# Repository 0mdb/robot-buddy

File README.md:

# Robot Buddy

A kid-safe, expressive robot platform combining real-time motor control, an animated TFT face, and optional networked AI planner.

## How It Works

Two ESP32-S3 microcontrollers handle the deterministic, safety-critical work: one drives motors with PID control and enforces safety limits, the other renders an animated face on a 320x240 TFT touch display (`esp32-face`). A Raspberry Pi 5 orchestrates everything at 50 Hz — reading sensors, running the state machine, applying layered safety policies, and streaming telemetry to a browser UI. An optional AI planner server on a separate machine (3090 Ti) generates expressive behavior plans via a local LLM.

Reflexes are local and deterministic. Planner is remote and optional.

## Hardware

| Component | Hardware | Role |
|---|---|---|
| Supervisor | Raspberry Pi 5 | 50 Hz orchestration, safety policy, HTTP/WS API |
| Face MCU | ESP32-S3 (Freenove FNK0104) | 320x240 TFT face renderer + touch/buttons telemetry |
| Reflex MCU | ESP32-S3 WROOM | Differential drive, PID, encoders, IMU, ultrasonic, safety |
| AI Server | PC with 3090 Ti (off-robot) | Planner/conversation LLM + TTS on LAN (`LLM_BACKEND=ollama|vllm`) |
| Motor Driver | TB6612FNG | Dual H-bridge for differential drive |
| Power | 2S LiPo | Split into dirty (motors) and clean 5V regulated rails |

## Repository Layout

```
robot-buddy/
├── supervisor/       # Python supervisor (Raspberry Pi 5, process-isolated workers)
│   ├── core/            # 50 Hz tick loop, state machine, safety, behavior engine
│   ├── devices/         # MCU clients (reflex, face), protocol, expressions
│   ├── io/              # Serial transport, COBS framing, CRC
│   ├── workers/         # Process-isolated workers (TTS, vision, AI)
│   ├── messages/        # NDJSON envelope, event/action types
│   ├── api/             # FastAPI HTTP/WebSocket server, param registry
│   ├── mock/            # Mock Reflex MCU for testing (PTY-based)
│   ├── tests/           # pytest test suite
│   └── pyproject.toml   # Package metadata, deps
├── server/              # AI planner server (3090 Ti, FastAPI + backend switch)
│   ├── app/             # FastAPI app, LLM/STT/TTS backends, prompts, schemas
│   ├── tests/           # pytest test suite
│   ├── Modelfile        # Legacy Ollama model config
│   └── pyproject.toml   # Package metadata, deps
├── esp32-face/       # Face MCU firmware (ESP32-S3, C/C++, ESP-IDF)
│   └── main/            # TFT face rendering + touch/buttons + USB protocol
├── esp32-reflex/        # Reflex MCU firmware (ESP32-S3, C/C++, ESP-IDF)
│   └── main/            # Differential drive, PID, IMU, safety, encoders
├── dashboard/           # React dashboard (Vite + TypeScript + Biome)
│   └── src/             # Components, hooks, stores, tabs
├── specs/               # Completed specifications (immutable reference)
├── docs/                # TODO, architecture, protocols, wiring, power, research
├── deploy/              # Deployment (systemd service, install/update scripts)
├── tools/               # Dev utilities (face sim V3, parity check)
└── training/            # Wake word model training
```

## Architecture

```
┌──────────────────────────────────────────────────────┐
│ On Robot                                             │
│                                                      │
│  ┌────────────────────────────────────────────────┐  │
│  │ Raspberry Pi 5 — Supervisor                    │  │
│  │                                                │  │
│  │  50 Hz tick loop:                              │  │
│  │    read telemetry → state machine → safety     │  │
│  │    policies → send commands → broadcast        │  │
│  │                                                │  │
│  │  HTTP API (:8080)  WebSocket (:8080/ws)        │  │
│  │  Vision process (separate OS process, 10-20Hz) │  │
│  └──────┬──────────────────────┬──────────────────┘  │
│         │ USB serial (COBS)    │ USB serial (COBS)   │
│  ┌──────▼──────┐        ┌─────▼───────┐             │
│  │ Reflex MCU  │        │  Face MCU   │             │
│  │ ESP32-S3    │        │  ESP32-S3   │             │
│  │             │        │             │             │
│  │ Motors, PID │        │ 320x240 TFT │             │
│  │ Encoders    │        │ Face +      │             │
│  │ IMU, Range  │        │ Touch UI    │             │
│  │ Safety      │        │             │             │
│  └─────────────┘        └─────────────┘             │
└──────────────────────────────────────────────────────┘
         │
         │ HTTP (LAN, optional)
         │
┌────────▼───────────────────────────┐
│ AI Server (3090 Ti PC)             │
│                                    │
│ FastAPI planner server             │
│ LLM backend: ollama | vllm         │
│ TTS: Orpheus (vLLM) + espeak shed  │
│ POST /plan / WS /converse /tts     │
└────────────────────────────────────┘
```

### State Machine

`BOOT` → `IDLE` → `TELEOP` / `WANDER` → `ERROR`

- **BOOT → IDLE**: automatic when Reflex MCU connects with no faults
- **IDLE → TELEOP/WANDER**: via `set_mode` command
- **Any → ERROR**: on disconnect, ESTOP, TILT, or BROWNOUT
- **ERROR → IDLE**: via `clear_error()` when Reflex is healthy

### Safety Policies (Defense in Depth)

1. Mode gate — no motion outside TELEOP/WANDER
2. Fault gate — any fault → zero twist
3. Reflex disconnect → zero twist
4. Ultrasonic range scaling (hard stop at 250 mm, 50% at 500 mm)
5. Stale range fallback (50% cap)
6. Vision confidence scaling
7. Stale vision timeout (500 ms)

Safety-critical enforcement also runs on the Reflex MCU itself (acceleration limits, command TTL, hard stop). The supervisor applies additional caps above this.

### Serial Protocol

Binary packets over USB serial with COBS framing:

```
[type:u8][seq:u8][payload:N][crc16:u16-LE]
```

For `esp32-face`, this protocol carries face state/gesture/system/talking commands and touch/button/status telemetry only. Audio transport is supervisor-side USB audio.

Auto-reconnect with exponential backoff (0.5s–5s). See `docs/protocols.md` for packet definitions.

## Tech Stack

| Component | Stack |
|---|---|
| Supervisor | Python 3.11+, asyncio, FastAPI, uvicorn, pyserial, OpenCV |
| AI Server | Python 3.11+, FastAPI, httpx, Pydantic, Ollama (compat) + vLLM (migration target) |
| ESP32 Firmware | C/C++, ESP-IDF (FreeRTOS), CMake |
| Build (Python) | Hatchling via pyproject.toml, uv for dependency management |
| Build (ESP32) | `idf.py build` (CMake), `source ~/esp/esp-idf/export.sh` |
| Dashboard | React 19, Vite, TypeScript, Zustand, TanStack Query |
| Tests | pytest, pytest-asyncio, Vitest |
| Linting | ruff (Python), clang-format + cppcheck (C++), Biome (TypeScript) |

## Getting Started

### Supervisor (Raspberry Pi 5)

```bash
cd supervisor
uv sync --group dev

# Run with mock hardware (no physical robot needed)
just run-mock

# Run with real hardware
just run

# Other options
uv run python -m supervisor --no-vision         # Disable vision worker
uv run python -m supervisor --http-port 8080    # Custom HTTP port
uv run python -m supervisor --planner-api http://10.0.0.20:8100 --robot-id robot-1
```

### AI Planner Server (3090 Ti PC)

```bash
# Install and run the server
cd server
uv sync --extra dev --extra llm --extra stt --extra tts

# Recommended testing profile (vLLM planner + CPU STT + espeak)
LLM_BACKEND=vllm STT_DEVICE=cpu TTS_BACKEND=espeak \
uv run --extra llm --extra stt --extra tts python -m app.main
```

The server starts on port 8100. See `server/README.md` for full API docs and configuration.

### ESP32 Firmware

Requires ESP-IDF toolchain.

```bash
cd esp32-face   # or esp32-reflex
idf.py build
idf.py flash
idf.py monitor
```

### Dashboard

```bash
just run-dashboard         # dev server with hot reload
just build-dashboard       # production build → supervisor/static/
```

## Development

All commands are available via `just` (see `justfile`):

```bash
just test-all              # run all tests (supervisor, server, dashboard)
just lint                  # check Python + C++ + dashboard
just lint-fix              # auto-fix formatting
just preflight             # full pre-commit check (lint + tests + parity)
just sim                   # run face simulator V3
just check-parity          # verify sim↔MCU constant alignment
```

### Mock Mode

The supervisor includes a PTY-based mock Reflex MCU (`supervisor/mock/mock_reflex.py`) that simulates serial communication, telemetry, and fault injection. Use `just run-mock` to run the full supervisor stack without any hardware.

### Dashboard

When the supervisor is running, open `http://<robot_ip>:8080` in a browser for:
- Live telemetry display with diagnostic tree
- Mode control (IDLE, TELEOP, WANDER)
- E-STOP button
- Face control (moods, gestures, talking, conversation state)
- Parameter tuning sliders (PID gains, speed limits, safety thresholds)
- Monitor tab (device health, comms, power, sensors, faults, workers)
- MJPEG video stream (if vision enabled)

### Configuration

**Supervisor** — YAML config file (schema in `supervisor/config.py`):
- Sections: serial, control, safety, network, logging, vision
- Default serial paths: `/dev/robot_reflex`, `/dev/robot_face` (via udev symlinks)

**AI Server** — environment variables:
- `LLM_BACKEND`, `VLLM_MODEL_NAME`, `LLM_MAX_INFLIGHT`, `PERFORMANCE_MODE`
- legacy compatibility: `OLLAMA_URL`, `MODEL_NAME`, `PLAN_TIMEOUT_S`, `TEMPERATURE`, `NUM_CTX`
- See `server/README.md` for the full table

**ESP32** — `sdkconfig.defaults` + `config.h` constants

## Supervisor API

| Endpoint | Method | Description |
|---|---|---|
| `/status` | GET | Current robot state (JSON) |
| `/params` | GET | Full parameter registry |
| `/params` | POST | Transactional parameter updates |
| `/actions` | POST | RPC: `set_mode`, `e_stop`, `clear_e_stop` |
| `/video` | GET | MJPEG stream (if vision enabled) |
| `/debug/devices` | GET | Device connection state |
| `/debug/planner` | GET | Planner state |
| `/debug/mcu_benchmark` | GET | MCU benchmark run status |
| `/ws` | WS | Telemetry stream (20 Hz, JSON) |
| `/ws/logs` | WS | Live log stream |

## AI Server API

| Endpoint | Method | Description |
|---|---|---|
| `/health` | GET | Server + selected LLM backend status |
| `/plan` | POST | Accept world state + `robot_id/seq/monotonic_ts_ms`, return plan + `plan_id` echo metadata |
| `/converse` | WS | Conversation stream (single active session per `robot_id`) |
| `/tts` | POST | Direct TTS with optional metadata (`robot_id`, `seq`, `monotonic_ts_ms`) |

Plan actions: `say(text)`, `emote(name, intensity)`, `gesture(name, params)`, `skill(name)` — planner proposes intent and supervisor executes deterministic skills.

## Supervisor Fallback Policy

| Failure condition | Immediate supervisor action | Motion policy | Face policy | Speech policy |
|---|---|---|---|---|
| `/plan` unreachable / non-200 | Mark planner disconnected; skip remote plan apply | Local deterministic only (`patrol_drift`/`avoid_obstacle`/safe stop) | `confused` gesture with cooldown | Cancel queued planner speech |
| `/converse` TTS fails mid-turn | Stop playback and clear talking flag | No change to motion authority | Show `thinking` briefly then restore previous mood | Attempt fallback backend once; if unavailable, skip speech |

## Project Status

### Working
- [x] Supervisor: 50 Hz control loop, state machine, safety policies, conversation state, mood choreography
- [x] Supervisor: serial transport with COBS framing, CRC, auto-reconnect, protocol v2 (timestamps + seq)
- [x] Supervisor: FastAPI HTTP/WebSocket API with telemetry streaming
- [x] Supervisor: process-isolated workers (TTS, vision, AI, ear)
- [x] Supervisor: mock Reflex MCU for hardware-free development
- [x] AI Server: FastAPI + vLLM planner (Qwen), conversation, TTS (Orpheus + espeak)
- [x] ESP32 Face: TFT face rendering, 13 moods, 13 gestures, conversation border, touch/button telemetry
- [x] ESP32 Reflex: motor control, PID, encoders, IMU, safety enforcement
- [x] Dashboard: React 19, live telemetry, face control, monitor tab, mode control
- [x] Voice pipeline: wake word ("hey buddy") + VAD → STT → LLM → TTS → face animation
- [x] WANDER mode driven by deterministic skills + planner intent
- [x] Deterministic telemetry: timestamps, sequence numbers, clock sync, raw packet logging

### In Progress
- [ ] Reflex MCU hardware commissioning (breadboard bring-up)
- [ ] Personality engine implementation (spec complete, implementation pending)

### Future
- [ ] Conversation memory / interaction history
- [ ] Wake word model improvements (recall 42% → 80%+)
- [ ] Additional modes: LINE_FOLLOW, BALL, CRANE, CHARGING
- [ ] Home Assistant integration
- [ ] Voice ID / speaker identification

See [docs/TODO.md](docs/TODO.md) for the detailed backlog and [specs/](specs/) for design specifications.

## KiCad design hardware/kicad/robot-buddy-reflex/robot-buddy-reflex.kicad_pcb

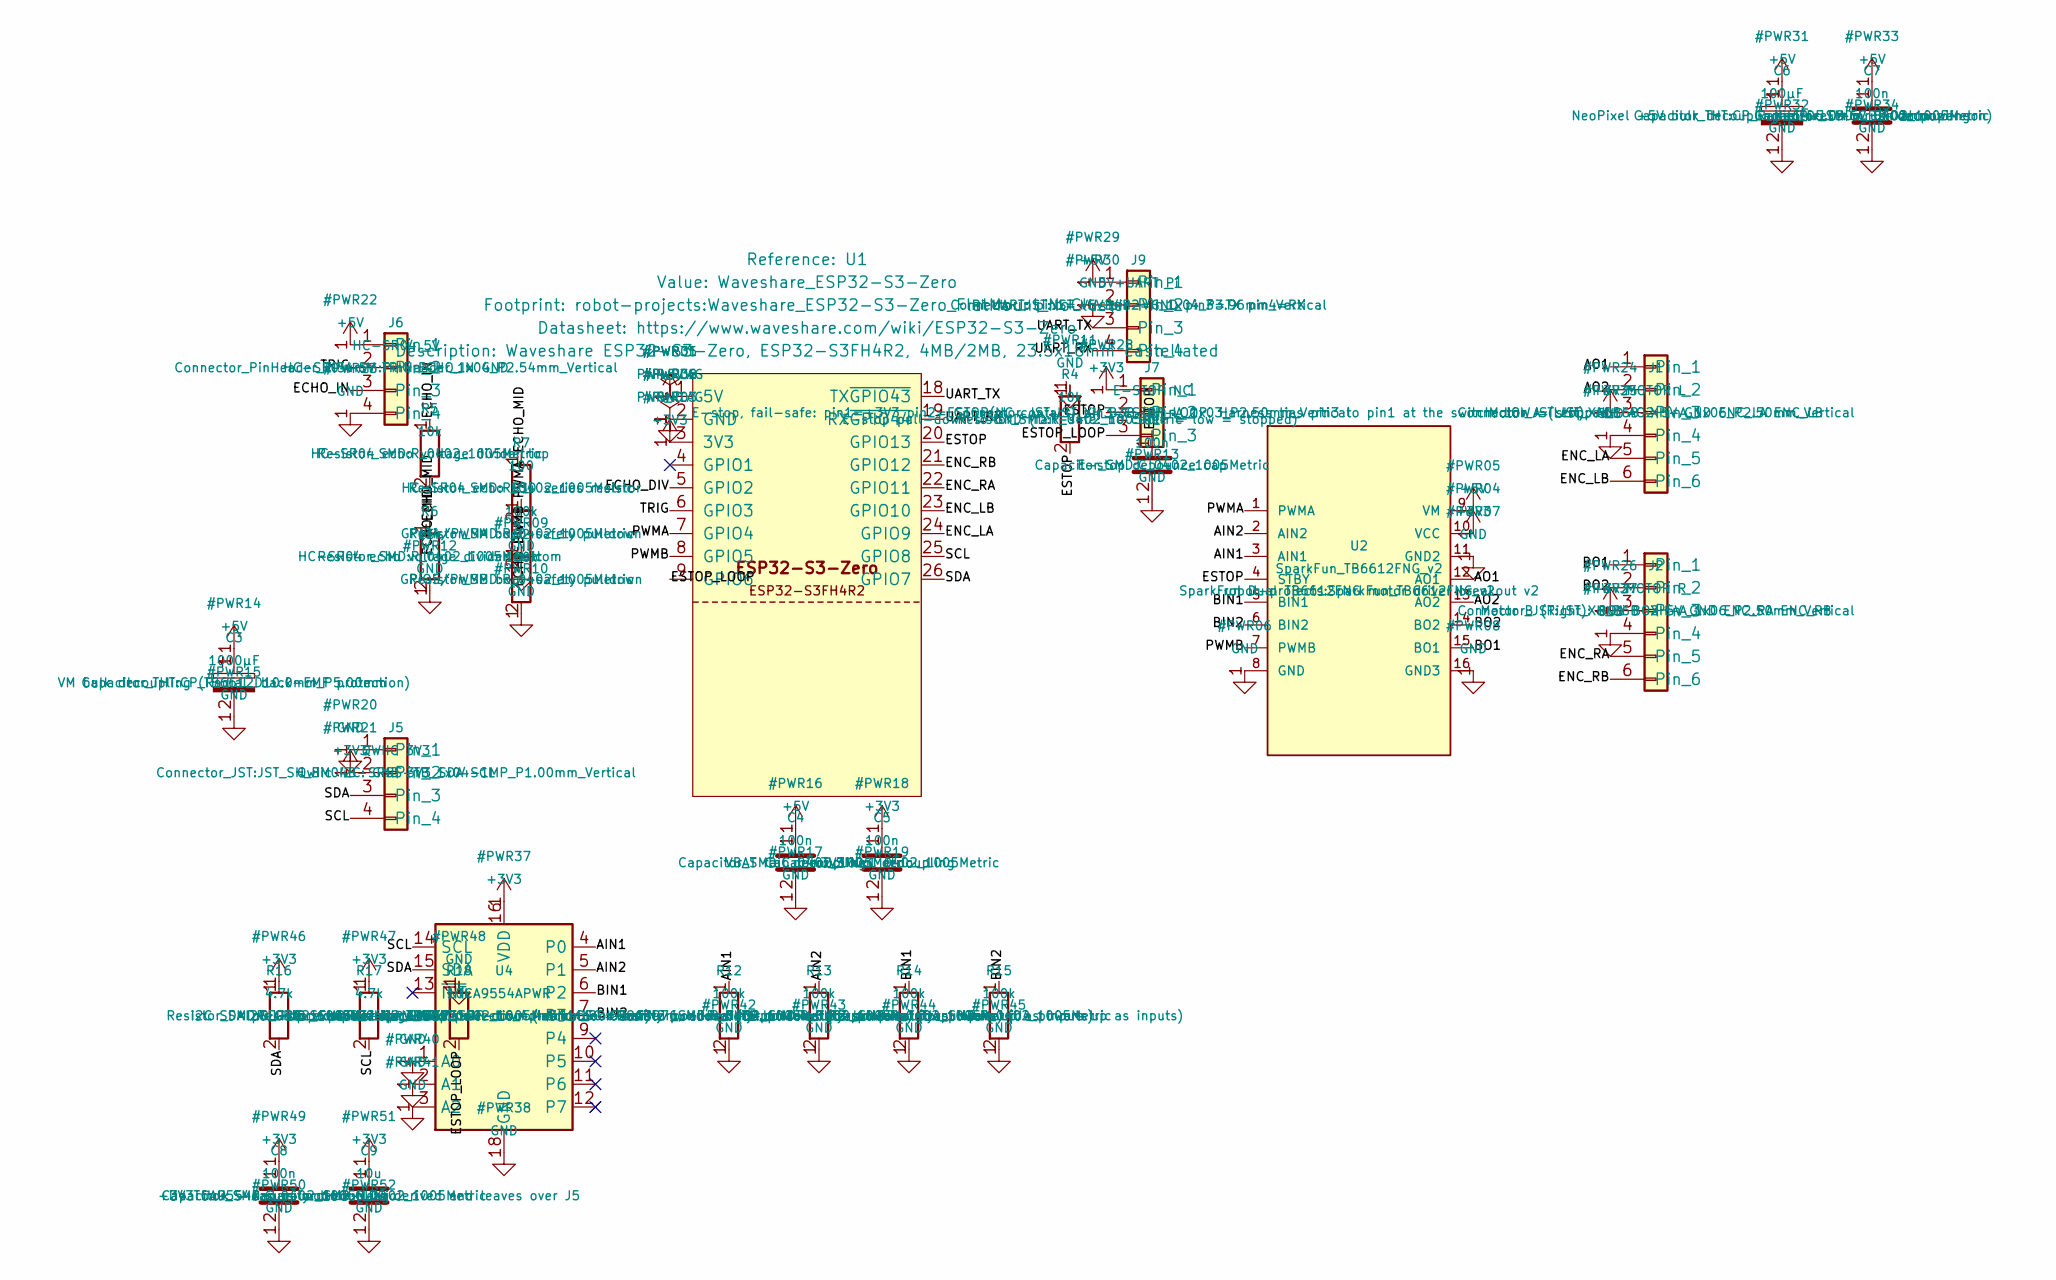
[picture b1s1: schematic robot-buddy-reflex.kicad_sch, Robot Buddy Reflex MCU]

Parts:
C1, C4, C5, C7, C8: 100n; C_0402_1005Metric
C3: 1000µF; CP_Radial_D10.0mm_P5.00mm
C6: 100µF; CP_Radial_D5.0mm_P2.00mm
C9: 10u; C_0402_1005Metric
J1: MOTOR L; JST_XH_B6B-XH-A_1x06_P2.50mm_Vertical
J2: MOTOR R; JST_XH_B6B-XH-A_1x06_P2.50mm_Vertical
J5: QWIIC 3V3; JST_SH_BM04B-SRSS-TB_1x04-1MP_P1.00mm_Vertical
J6: HC-SR04 5V; PinHeader_1x04_P2.54mm_Vertical
J7: E-STOP NC; JST_XH_B3B-XH-A_1x03_P2.50mm_Vertical
J9: 5V+UART Pi; JST_VH_B4P-VH_1x04_P3.96mm_Vertical
R1, R2, R12, R13, R14, R15: 100k; R_0402_1005Metric
R4, R5, R18: 10k; R_0402_1005Metric
R6: 15k; R_0402_1005Metric
R7: 100; R_0402_1005Metric
R16, R17: 4.7k; R_0402_1005Metric
U1: Waveshare_ESP32-S3-Zero; Waveshare_ESP32-S3-Zero_FlatMount_NoCluster
U2: SparkFun_TB6612FNG_v2
U4: TCA9554APWR; TSSOP-16_4.4x5mm_P0.65mm

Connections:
+3V3: C5.1, C8.1, C9.1, J1.3, J2.3, J5.2, J7.1, R16.1, R17.1, U1.3 (3V3), U2.10 (VCC), U4.16 (VDD)
/AIN1: R12.1, U2.3 (AIN1), U4.4 (P0)
/AIN2: R13.1, U2.2 (AIN2), U4.5 (P1)
/AO1: J1.1, U2.12 (AO1)
/AO2: J1.2, U2.13 (AO2)
/BIN1: R14.1, U2.5 (BIN1), U4.6 (P2)
/BIN2: R15.1, U2.6 (BIN2), U4.7 (P3)
/BO1: J2.1, U2.15 (BO1)
/BO2: J2.2, U2.14 (BO2)
/ECHO_DIV: R7.2, U1.5 (GPIO2)
/ECHO_IN: J6.3, R5.1
/ECHO_MID: R5.2, R6.1, R7.1
/ENC_LA: J1.5, U1.24 (GPIO9)
/ENC_LB: J1.6, U1.23 (GPIO10)
/ENC_RA: J2.5, U1.22 (GPIO11)
/ENC_RB: J2.6, U1.21 (GPIO12)
/ESTOP: C1.1, J7.2, R4.2, U1.20 (GPIO13), U2.4 (STBY)
/ESTOP_LOOP: J7.3, R18.2, U1.9 (GPIO6)
/PWMA: R1.1, U1.7 (GPIO4), U2.1 (PWMA)
/PWMB: R2.1, U1.8 (GPIO5), U2.7 (PWMB)
/SCL: J5.4, R17.2, U1.25 (GPIO8), U4.14 (SCL)
/SDA: J5.3, R16.2, U1.26 (GPIO7), U4.15 (SDA)
/TRIG: J6.2, U1.6 (GPIO3)
/UART_RX: J9.4, U1.19 (RX~GPIO44)
/UART_TX: J9.3, U1.18 (TX~GPIO43)

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
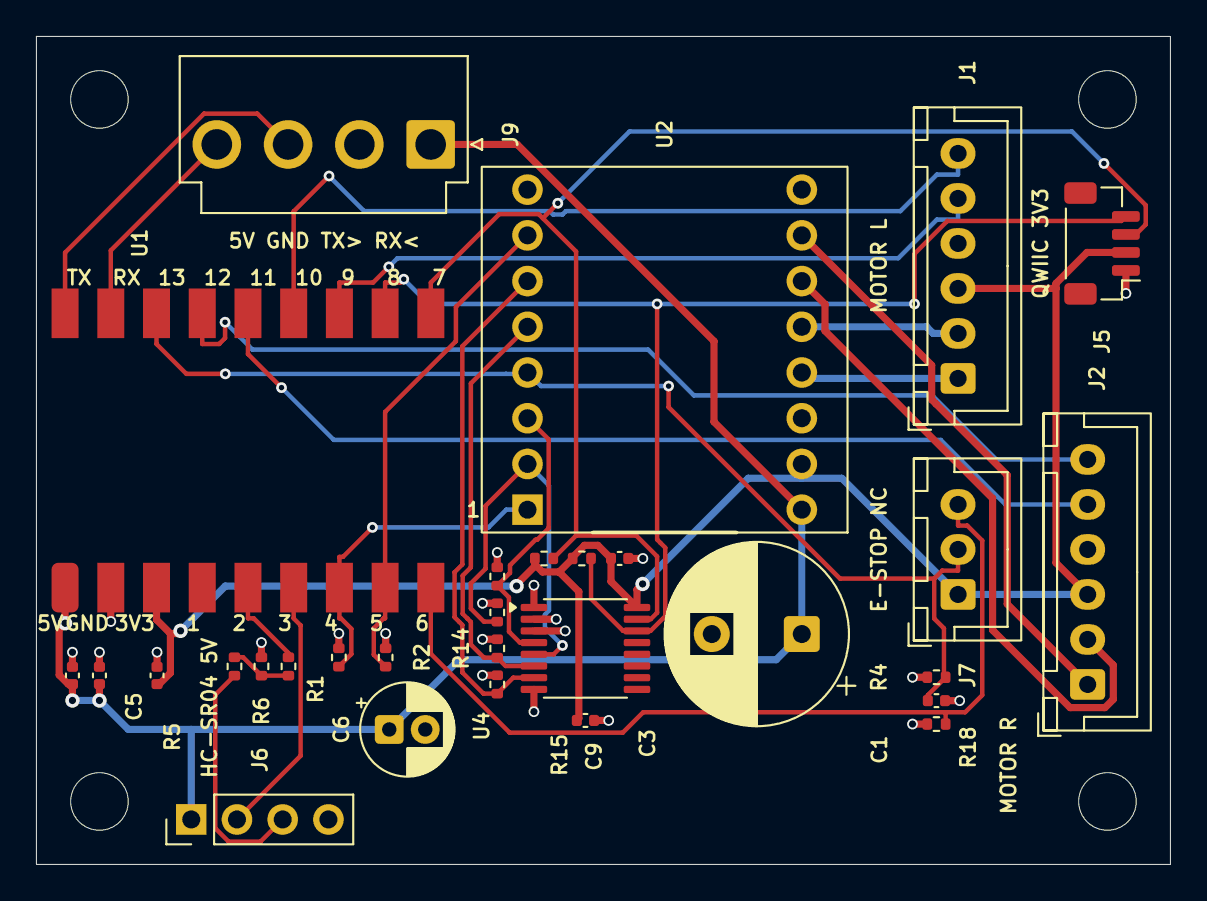
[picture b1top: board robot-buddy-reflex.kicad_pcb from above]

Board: 4 copper layers, 63.0 x 46.0 mm, 34 parts (0 on the bottom side), 27 nets.

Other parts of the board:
MH1, MH2, MH3, MH4: MountingHole; MountingHole_3.2mm_M3_DIN965

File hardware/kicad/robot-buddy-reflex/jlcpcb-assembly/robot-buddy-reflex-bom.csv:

Comment,Designator,Footprint,JLCPCB Part # (LCSC)
100,R7,R_0402_1005Metric,C25076
100k,"R1,R12,R13,R14,R15,R2",R_0402_1005Metric,C25741
100n,"C1,C4,C5,C7,C8",C_0402_1005Metric,C1525
10k,"R18,R4,R5",R_0402_1005Metric,C25744
10u,C9,C_0402_1005Metric,C15525
15k,R6,R_0402_1005Metric,C25756
4.7k,"R16,R17",R_0402_1005Metric,C25900
QWIIC 3V3,J5,JST_SH_BM04B-SRSS-TB_1x04-1MP_P1.00mm_Vertical,C160390
TCA9554APWR,U4,TSSOP-16_4.4x5mm_P0.65mm,C2863976

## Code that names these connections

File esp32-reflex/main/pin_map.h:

#pragma once
// GPIO assignments — Reflex MCU (Waveshare ESP32-S3-Zero on robot-buddy-reflex v2).
// All pin choices in one place. Must match the board: hardware/kicad/pcb_qc.py §3
// checks every PIN_* here against the schematic netlist.
//
// v2 board (docs/v2-defect-register.md §A0, §M11): the module is soldered flat with its
// PERIMETER pads only (no underside cluster), so GPIO17/18/38/39 are gone. The four
// TB6612 direction lines moved to a TCA9554A I²C expander (U4), and TB6612 STBY is tied
// to the hardware e-stop net, not to a GPIO.

#include "driver/gpio.h"

#include <cstdint>

// ---- Motor driver (TB6612FNG) ----
// PWM outputs (LEDC channels). U1 pads 7/8. R1/R2 100k pull-downs hold them low at boot.
constexpr gpio_num_t PIN_PWMA = GPIO_NUM_4; // left motor PWM
constexpr gpio_num_t PIN_PWMB = GPIO_NUM_5; // right motor PWM

// Direction lines are TCA9554A port bits, not GPIOs (U4: P0-P3 = U4 pins 4-7).
// The expander powers up with every port an input; R12-R15 100k pull-downs hold all
// four lines low until firmware drives them (register A2: power-up state is a safety
// property). Set a direction only through motor.cpp, which sequences PWM around it.
constexpr uint8_t EXP_I2C_ADDR = 0x38;    // TCA9554A, A2..A0 = GND
constexpr uint8_t EXP_BIT_AIN1 = 1u << 0; // P0: left fwd
constexpr uint8_t EXP_BIT_AIN2 = 1u << 1; // P1: left rev
constexpr uint8_t EXP_BIT_BIN1 = 1u << 2; // P2: right fwd
constexpr uint8_t EXP_BIT_BIN2 = 1u << 3; // P3: right rev
constexpr uint8_t EXP_DIR_MASK = 0x0F;    // P4-P7 unconnected (stay inputs)

// ---- Encoders (quadrature, directly to PCNT) ----
// Powered from +3V3 on v2 (register M7): A/B are 3.3 V logic into these pins.
constexpr gpio_num_t PIN_ENC_L_A = GPIO_NUM_9;
constexpr gpio_num_t PIN_ENC_L_B = GPIO_NUM_10;
constexpr gpio_num_t PIN_ENC_R_A = GPIO_NUM_11;
constexpr gpio_num_t PIN_ENC_R_B = GPIO_NUM_12;

// ---- Shared I²C bus: BMI270 IMU (via Qwiic J5) + TCA9554A expander (U4) ----
// U1 pads 26/25. R16/R17 4.7k pull-ups to +3V3 on the board. One bus, owned by
// i2c_bus.cpp; both devices hang off it.
constexpr gpio_num_t PIN_I2C_SDA = GPIO_NUM_7;
constexpr gpio_num_t PIN_I2C_SCL = GPIO_NUM_8;
// Names the IMU code (and pcb_qc.py) use for the same two pins.
constexpr gpio_num_t PIN_IMU_SDA = PIN_I2C_SDA;
constexpr gpio_num_t PIN_IMU_SCL = PIN_I2C_SCL;

// ---- Ultrasonic range sensor (HC-SR04) ----
constexpr gpio_num_t PIN_RANGE_TRIG = GPIO_NUM_3; // output: 10 µs trigger pulse
constexpr gpio_num_t PIN_RANGE_ECHO = GPIO_NUM_2; // input: echo via the R5/R6 divider

// ---- E-stop (register E3: fail-safe, with cable detect) ----
// /ESTOP: +3V3 through the NC contact. HIGH = switch intact, robot may run.
// LOW = stopped (pressed or cable missing; R4 pulls it down). The same net drives TB6612
// STBY directly, so the hardware kill needs no firmware; this pin is for reporting.
constexpr gpio_num_t PIN_ESTOP_N = GPIO_NUM_13; // active-low, external pull-DOWN (R4)
// /ESTOP_LOOP: J7 pin 3, tied to pin 1 (+3V3) at the switch in the harness.
// HIGH = cable present; LOW = cable missing (R18 pull-down).
constexpr gpio_num_t PIN_ESTOP_LOOP = GPIO_NUM_6;

// Battery voltage sense is Pi-side (Waveshare UPS HAT (B) INA219 over I²C), see
// docs/power.md. GPIO1 (U1 pad 4) is free.
